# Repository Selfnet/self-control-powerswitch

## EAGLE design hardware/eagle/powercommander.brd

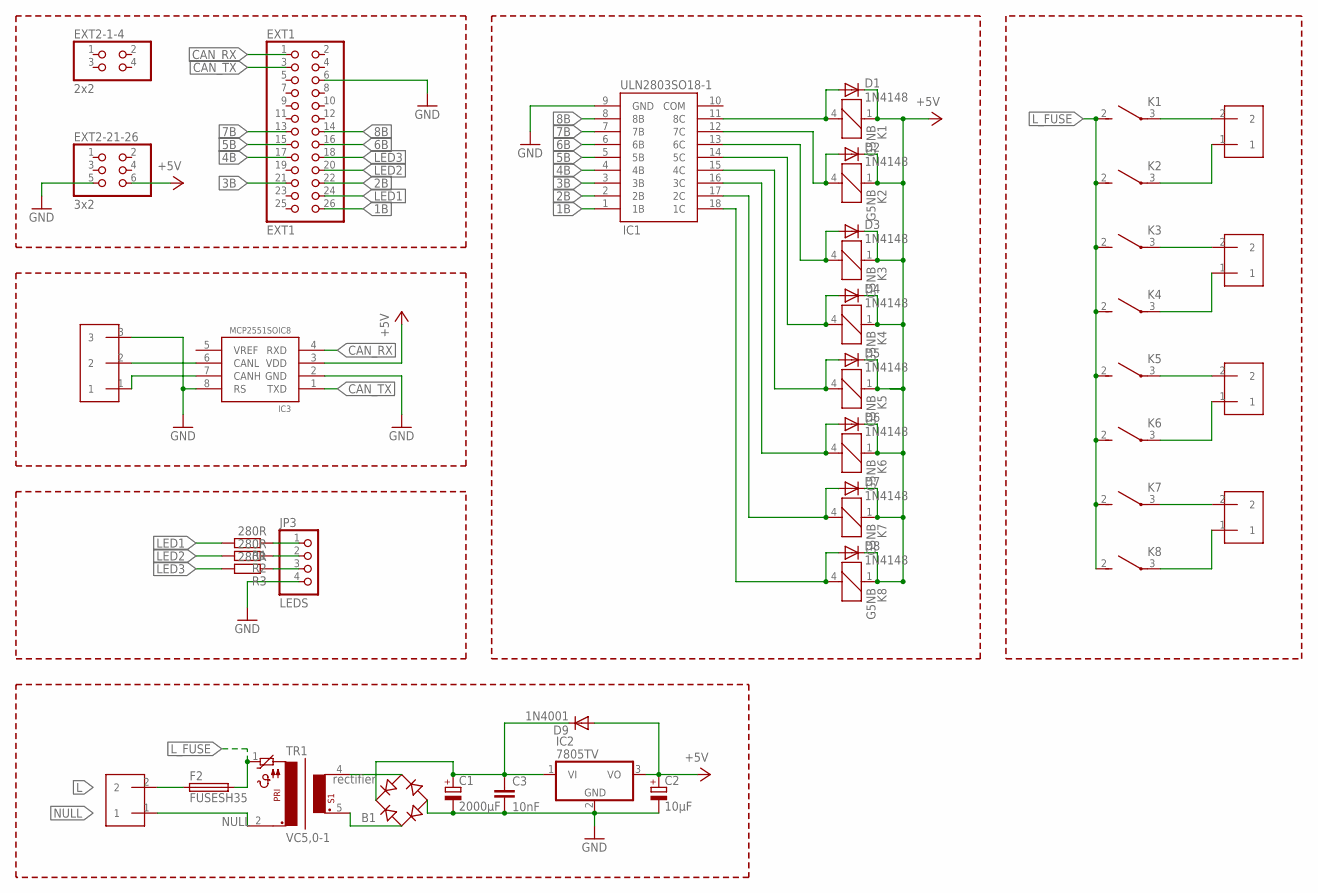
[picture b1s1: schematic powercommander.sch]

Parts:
B1: rectifier; RB1A
C1: 2000µF; E5-8,5
C2: 10µF; E5-8,5
C3: 10nF; C025-025X050
D1, D2, D3, D4, D5, D6, D7, D8: 1N4148; SOD323-W
D9: 1N4001; MELF-MLL41
EXT1: EXT1; 2X13
EXT2-1-4: 2x2; 2X02
EXT2-21-26: 3x2; 2X03
F2: FUSESH35; SH25
IC1: ULN2803SO18-1; SO18-1
IC2: 7805TV; TO220V
IC3: MCP2551SOIC8; SOIC-08LG
JP3: LEDS; 1X04
K1, K2, K3, K4, K5, K6, K7, K8: G5NB
PHASE: 2KLEMME; W237-102
R1, R2, R3: 280R; 0204/7
TR1: VC5,0-1
X2: 3KLEMME; W237-103
X3, X4, X5, X6: 2KLEMME; W237-102

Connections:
1B: EXT1.26, IC1.1 (1B)
2B: EXT1.22, IC1.2 (2B)
3B: EXT1.21, IC1.3 (3B)
4B: EXT1.17, IC1.4 (4B)
5B: EXT1.15, IC1.5 (5B)
6B: EXT1.16, IC1.6 (6B)
7B: EXT1.13, IC1.7 (7B)
8B: EXT1.14, IC1.8 (8B)
+5V: C2.+, D1.C, D2.C, D3.C, D4.C, D5.C, D6.C, D7.C, D8.C, D9.A, EXT2-21-26.6, IC2.3 (VO), IC3.3 (VDD), K1.1, K2.1, K3.1, K4.1, K5.1, K6.1, K7.1, K8.1
A1: K1.3, X3.2
A3: K3.3, X4.2
A5: K5.3, X5.2
A7: K7.3, X6.2
CAN_RX: EXT1.1, IC3.4 (RXD)
CAN_TX: EXT1.3, IC3.1 (TXD)
GND: B1.-, C1.-, C2.-, C3.2, EXT1.6, EXT2-21-26.5, IC1.9 (GND), IC2.2 (GND), IC3.2 (GND), IC3.8 (RS), JP3.4, X2.3
L: F2.1, PHASE.2
LED1: EXT1.24, R1.2
LED2: EXT1.20, R2.2
LED3: EXT1.18, R3.2
L_FUSE: F2.2, K1.2, K2.2, K3.2, K4.2, K5.2, K6.2, K7.2, K8.2, TR1.1
unnamed: IC3.7 (CANH), X2.1
unnamed: B1.AC2, TR1.4
unnamed: B1.AC1, TR1.5 (3)
unnamed: B1.+, C1.+, C3.1, D9.C, IC2.1 (VI)
unnamed: IC3.6 (CANL), X2.2
unnamed: K4.3, X4.1
unnamed: D2.A, IC1.12 (7C), K2.4
unnamed: D3.A, IC1.13 (6C), K3.4
unnamed: K6.3, X5.1
unnamed: K8.3, X6.1
unnamed: K2.3, X3.1
unnamed: D7.A, IC1.17 (2C), K7.4
unnamed: D1.A, IC1.11 (8C), K1.4
unnamed: D8.A, IC1.18 (1C), K8.4
unnamed: D6.A, IC1.16 (3C), K6.4
unnamed: D5.A, IC1.15 (4C), K5.4
unnamed: D4.A, IC1.14 (5C), K4.4
unnamed: JP3.1, R1.1
unnamed: JP3.2, R2.1
unnamed: JP3.3, R3.1
NULL: PHASE.1, TR1.2

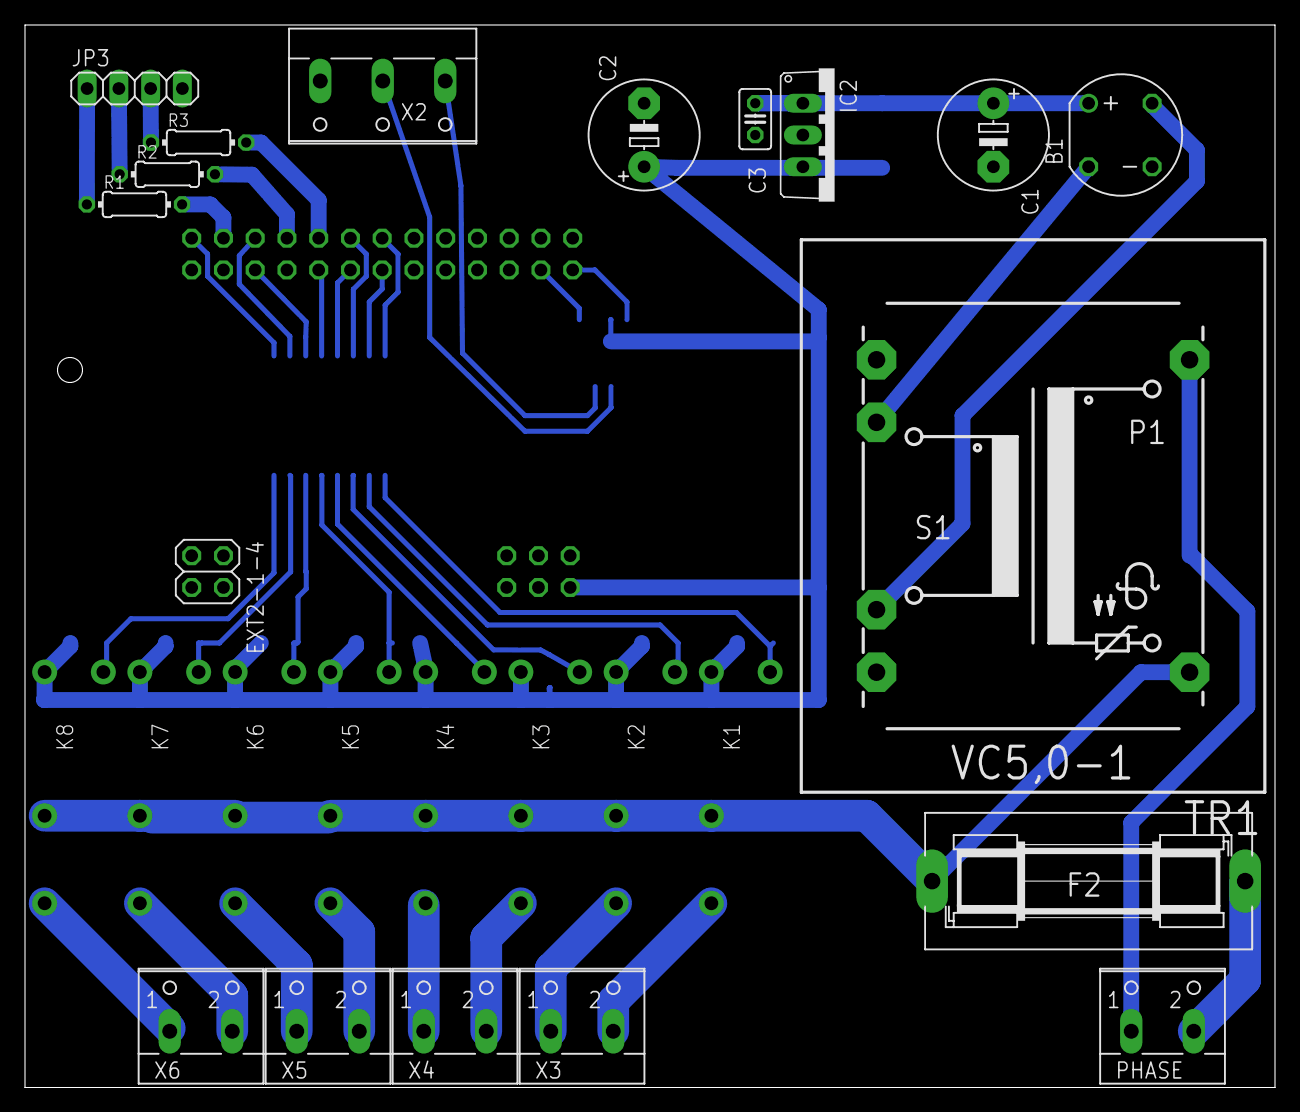
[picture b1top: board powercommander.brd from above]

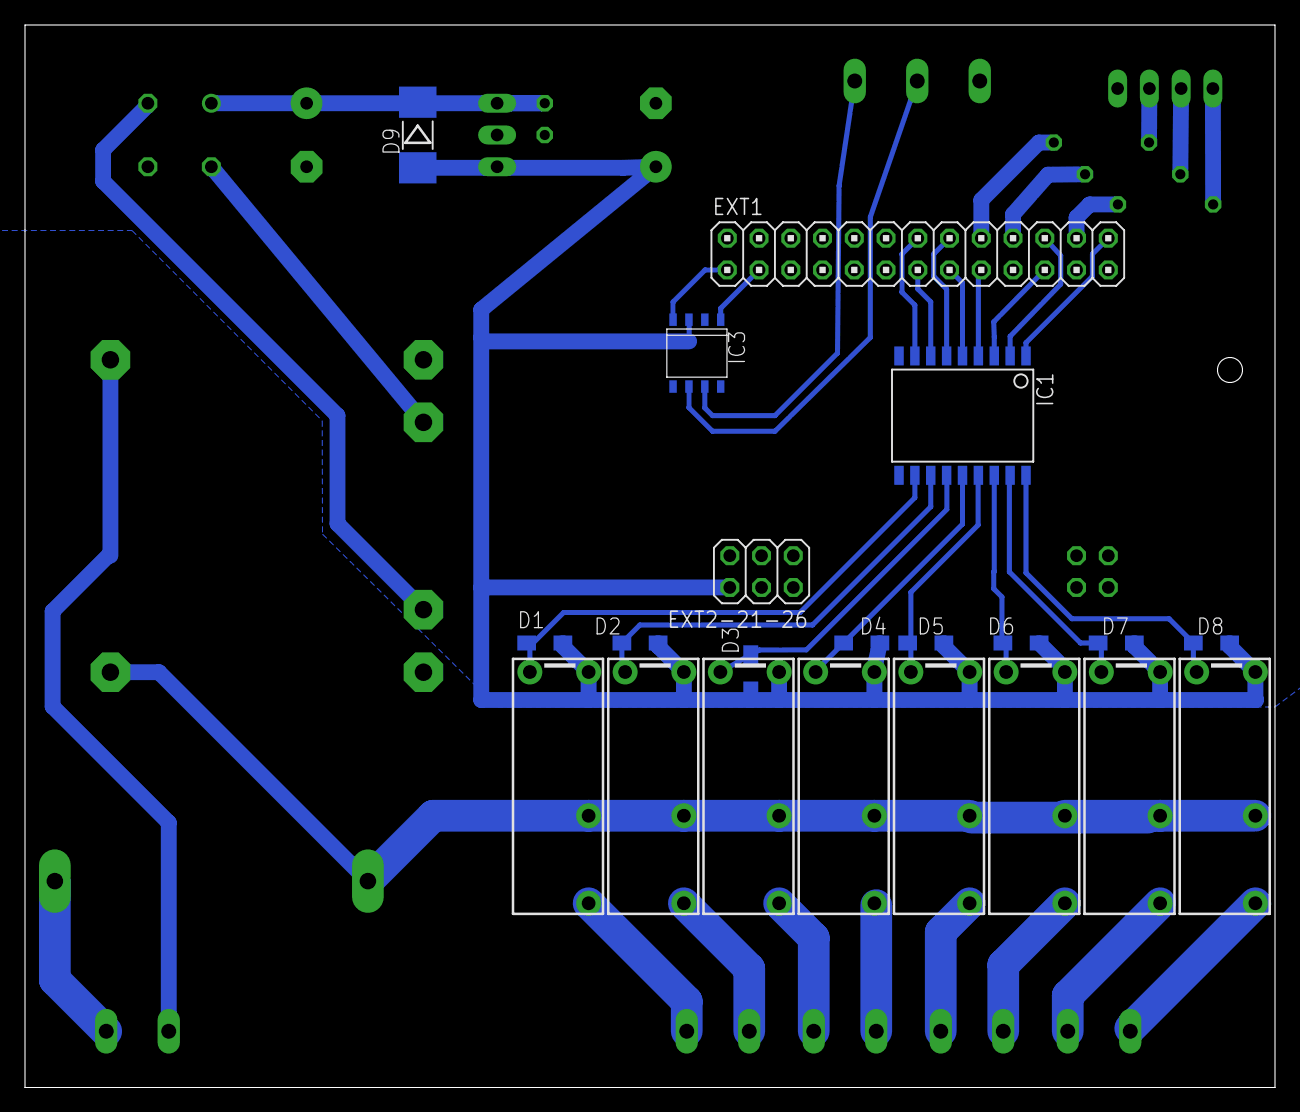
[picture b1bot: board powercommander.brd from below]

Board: 2 copper layers, 100.0 x 85.0 mm, 39 parts (13 on the bottom side), 42 nets.

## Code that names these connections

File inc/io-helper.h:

#ifndef __IO_HELPER_H__
#define __IO_HELPER_H__

#include "stm32f10x.h"


#define UI32_DELAY_TIME 0x1FFFFF

#define BUTTON_1_PIN    GPIO_Pin_0
#define BUTTON_1_PORT   GPIOA
#define BUTTON_1_CLK    RCC_APB2Periph_GPIOA

#define KEY_PRESSED     0x00
#define KEY_NOT_PRESSED 0x01

//onboard
#define LED0_PIN        GPIO_Pin_12
#define LED0_GPIO_PORT  GPIOC
#define LED0_GPIO_CLK   RCC_APB2Periph_GPIOC

//gruen
#define LED1_PIN        GPIO_Pin_13 //PC13  EXT1-24
#define LED1_GPIO_PORT  GPIOC
#define LED1_GPIO_CLK   RCC_APB2Periph_GPIOC

#define LED2_PIN        GPIO_Pin_1 //PC1    EXT1-20
#define LED2_GPIO_PORT  GPIOC
#define LED2_GPIO_CLK   RCC_APB2Periph_GPIOC

//rot
#define LED3_PIN        GPIO_Pin_5 //PB8    EXT1-18
#define LED3_GPIO_PORT  GPIOA
#define LED3_GPIO_CLK   RCC_APB2Periph_GPIOA

//Buttons
void button_init(void);
uint32_t Button_GetState(uint32_t);

// Can functions
void CAN_config(void);

// Led
void LED_init(void);
void LED_On(uint32_t lednr);
void LED_Off(uint32_t lednr);
void LED_Toggle(uint32_t lednr);

#endif

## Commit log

2013-05-19 test
2013-05-19 initial commit of fucked up board design.
2013-05-19 sicherheits kopien von eagle geloescht
2013-05-19 gitignore added
2013-05-19 added personal parts lib
2013-05-19 *.[s|b]## to gitignore added
2013-05-19 corrected screw terminal center point added mcp2551 smd variant
2013-05-19 modified mcp2551-smd: wider pads and placement dot
2013-05-19 neu verkabelt
2013-05-19 neue board version mit pwm pins
2013-05-20 some fixes..
2013-05-20 removed transformer holes
2013-05-20 board and schematic fancyfied
2013-05-20 compatibility rename
2013-05-20 klemme angepasst
2013-05-20 code + datasheet added
2013-05-22 working code, with pwm and timer
2013-06-21 new boardlayout + pwm für relay added
2013-06-21 cleaned up
2013-08-25 added support for Eltako serial protocol
2013-08-31 Weitergetüddelt, tut grad mal wieder
2013-08-31 ziemlich kaputt grad
